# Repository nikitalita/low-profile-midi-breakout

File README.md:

# low-profile-midi-breakout

low vertical profile midi breakout board, for front panel mounting. 3.3v only!

# WARNING: COMPLETELY UNTESTED

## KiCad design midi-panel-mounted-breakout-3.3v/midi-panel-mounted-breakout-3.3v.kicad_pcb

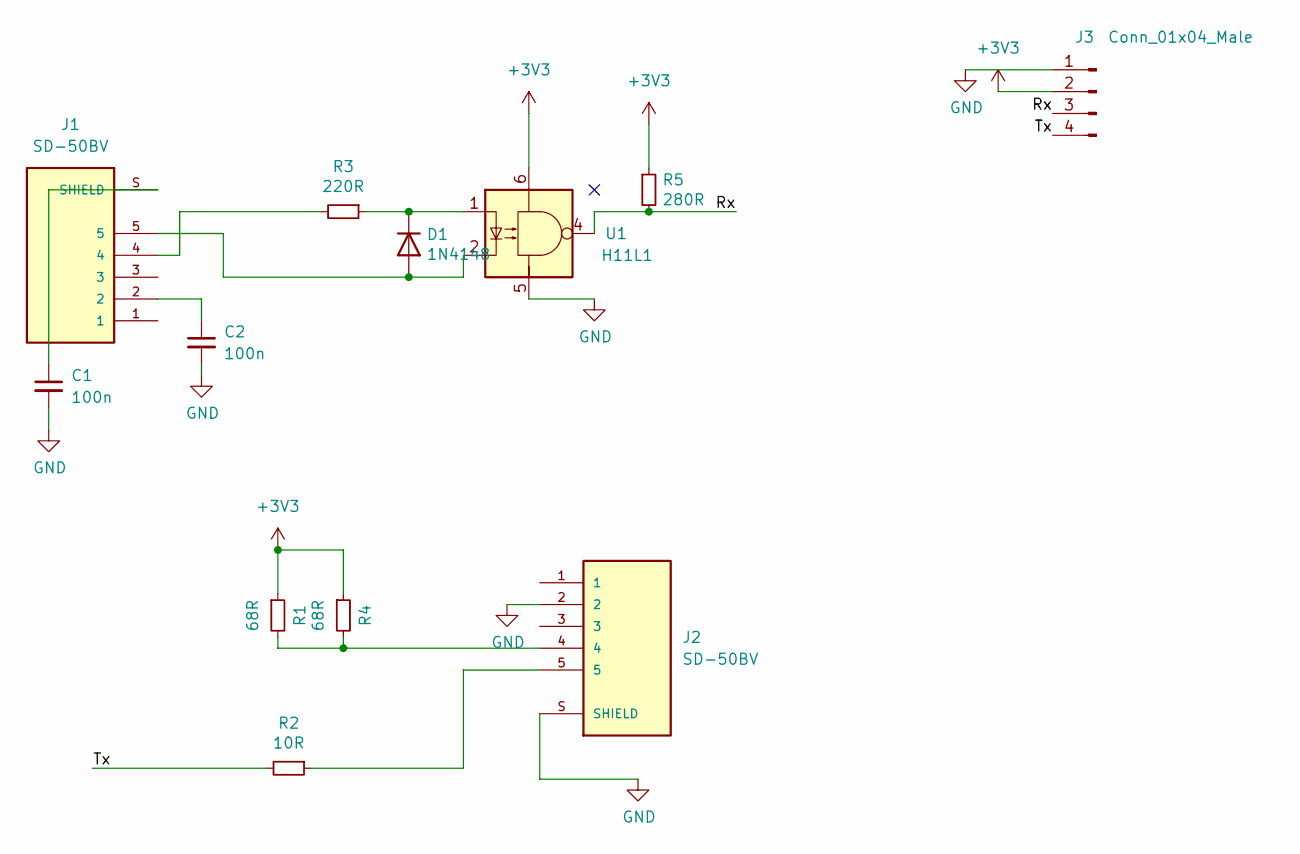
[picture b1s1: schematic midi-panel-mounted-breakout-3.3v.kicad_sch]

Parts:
C1, C2: 100n; C_0402_1005Metric
D1: 1N4148; D_0805_2012Metric
J1, J2: SD-50BV; CUI_SD-50BV; PARTREV 1.03
J3: Conn_01x04_Male; PinHeader_1x04_P2.54mm_Vertical
R1, R4: 68R; R_0402_1005Metric; Mouser 667-ERJ-6ENF2200V
R2: 10R; R_0402_1005Metric; Mouser 667-ERJ-6ENF2200V
R3: 220R; R_0402_1005Metric; Mouser 667-ERJ-6ENF2200V
R5: 280R; R_0402_1005Metric; Mouser 667-ERJ-6ENF1002V
U1: H11L1; Everlight_H11L1S

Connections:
+3V3: J3.2, R1.1, R4.1, R5.1, U1.6
/Rx: J3.3, R5.2, U1.4
/Tx: J3.4, R2.2
GND: C1.2, C2.2, J2.2, J2.S (SHIELD), J3.1, U1.5
unnamed: C1.1, J1.S (SHIELD)
unnamed: C2.1, J1.2
unnamed: D1.1 (K), R3.1, U1.1
unnamed: D1.2 (A), J1.5, U1.2
unnamed: J1.4, R3.2
unnamed: J2.4, R1.2, R4.2
unnamed: J2.5, R2.1

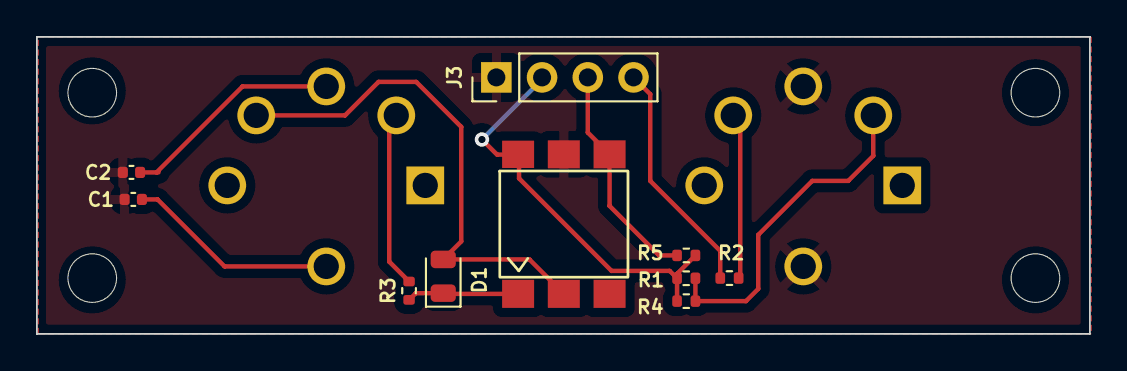
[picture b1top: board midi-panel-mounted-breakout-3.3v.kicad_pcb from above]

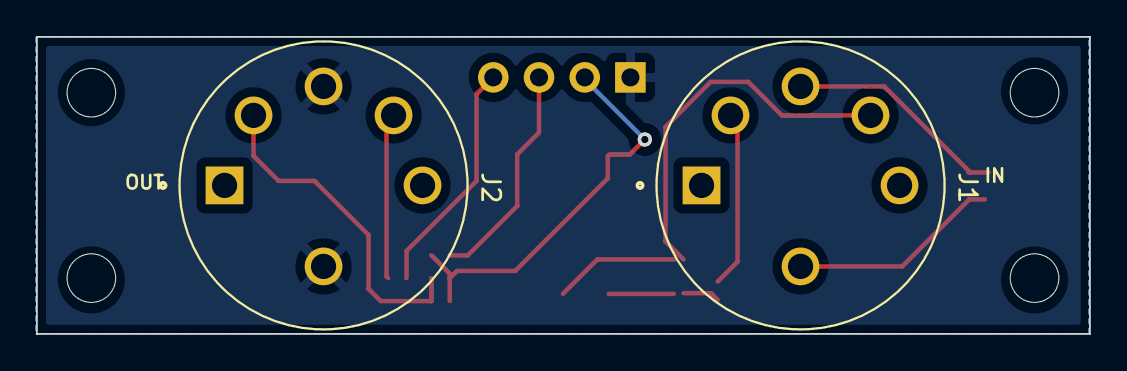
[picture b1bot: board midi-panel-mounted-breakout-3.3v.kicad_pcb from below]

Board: 2 copper layers, 58.5 x 16.5 mm, 12 parts (2 on the bottom side), 11 nets.

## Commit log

2023-02-08 WIP-changes
